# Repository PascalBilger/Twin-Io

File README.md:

# Twin-Io
A wireless multi lead ECG

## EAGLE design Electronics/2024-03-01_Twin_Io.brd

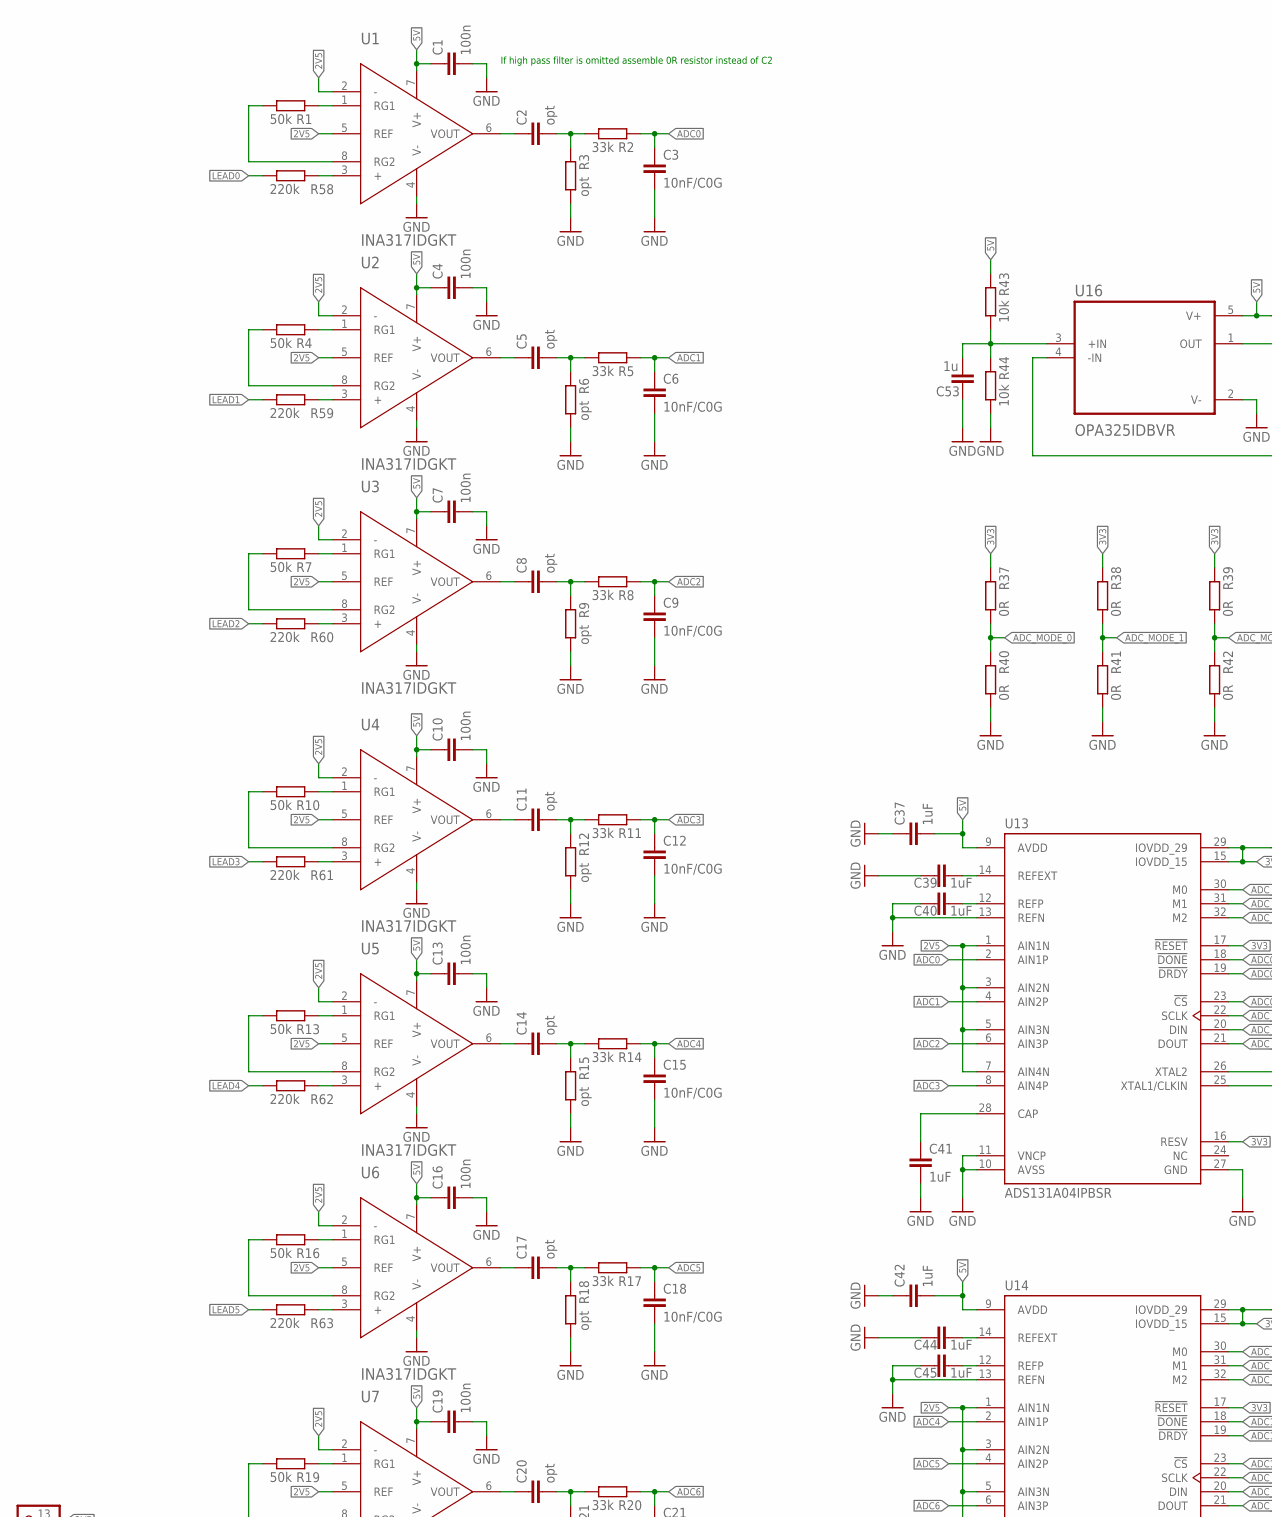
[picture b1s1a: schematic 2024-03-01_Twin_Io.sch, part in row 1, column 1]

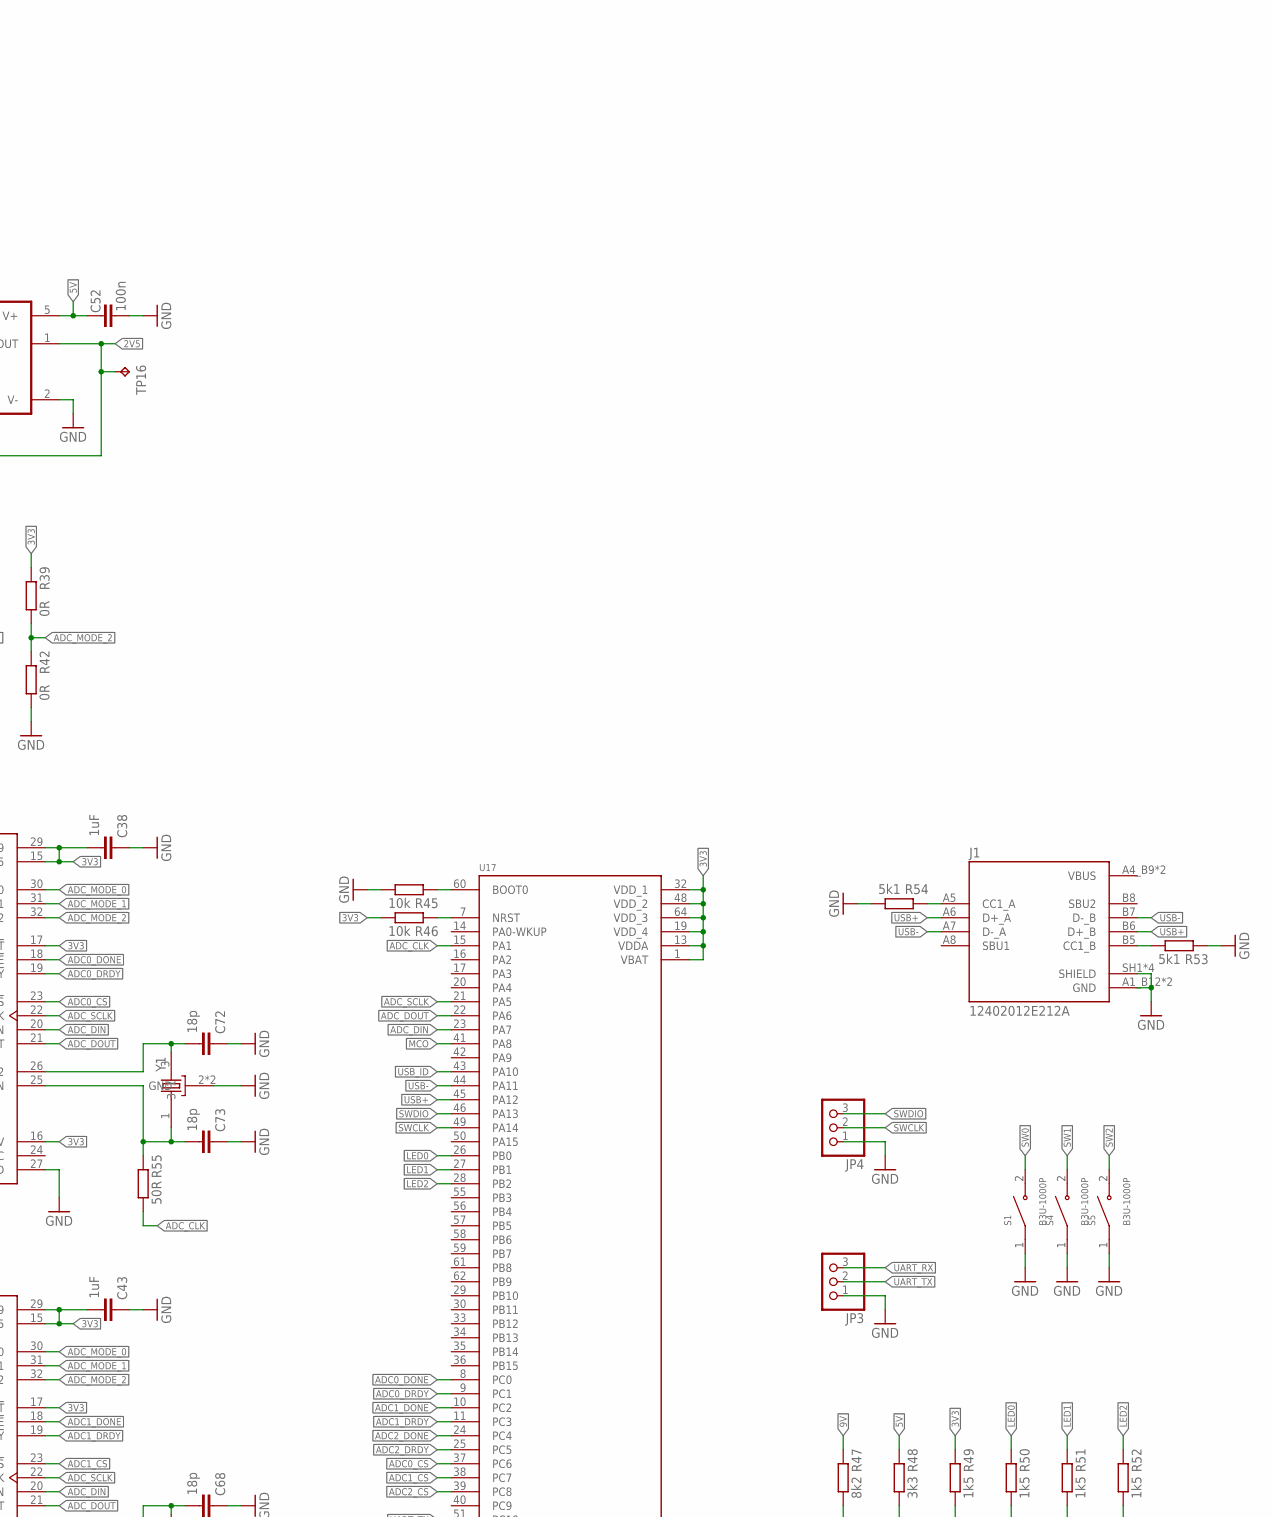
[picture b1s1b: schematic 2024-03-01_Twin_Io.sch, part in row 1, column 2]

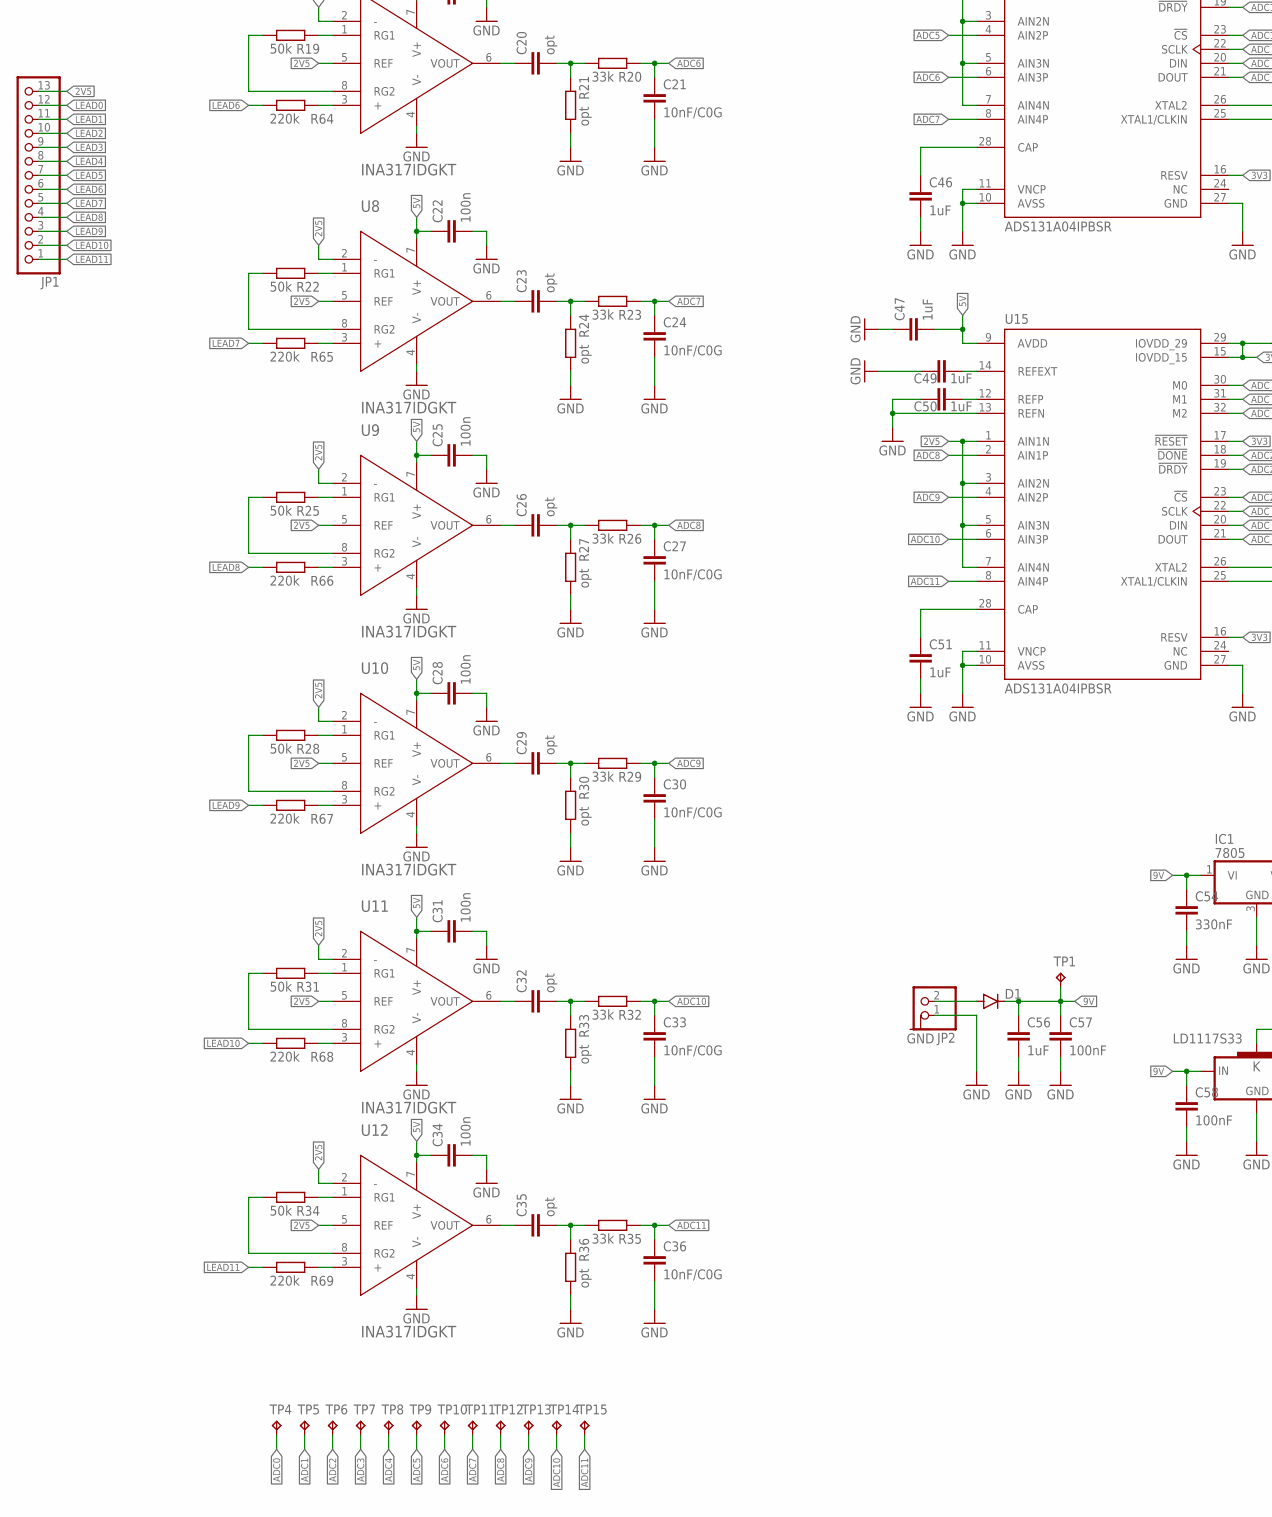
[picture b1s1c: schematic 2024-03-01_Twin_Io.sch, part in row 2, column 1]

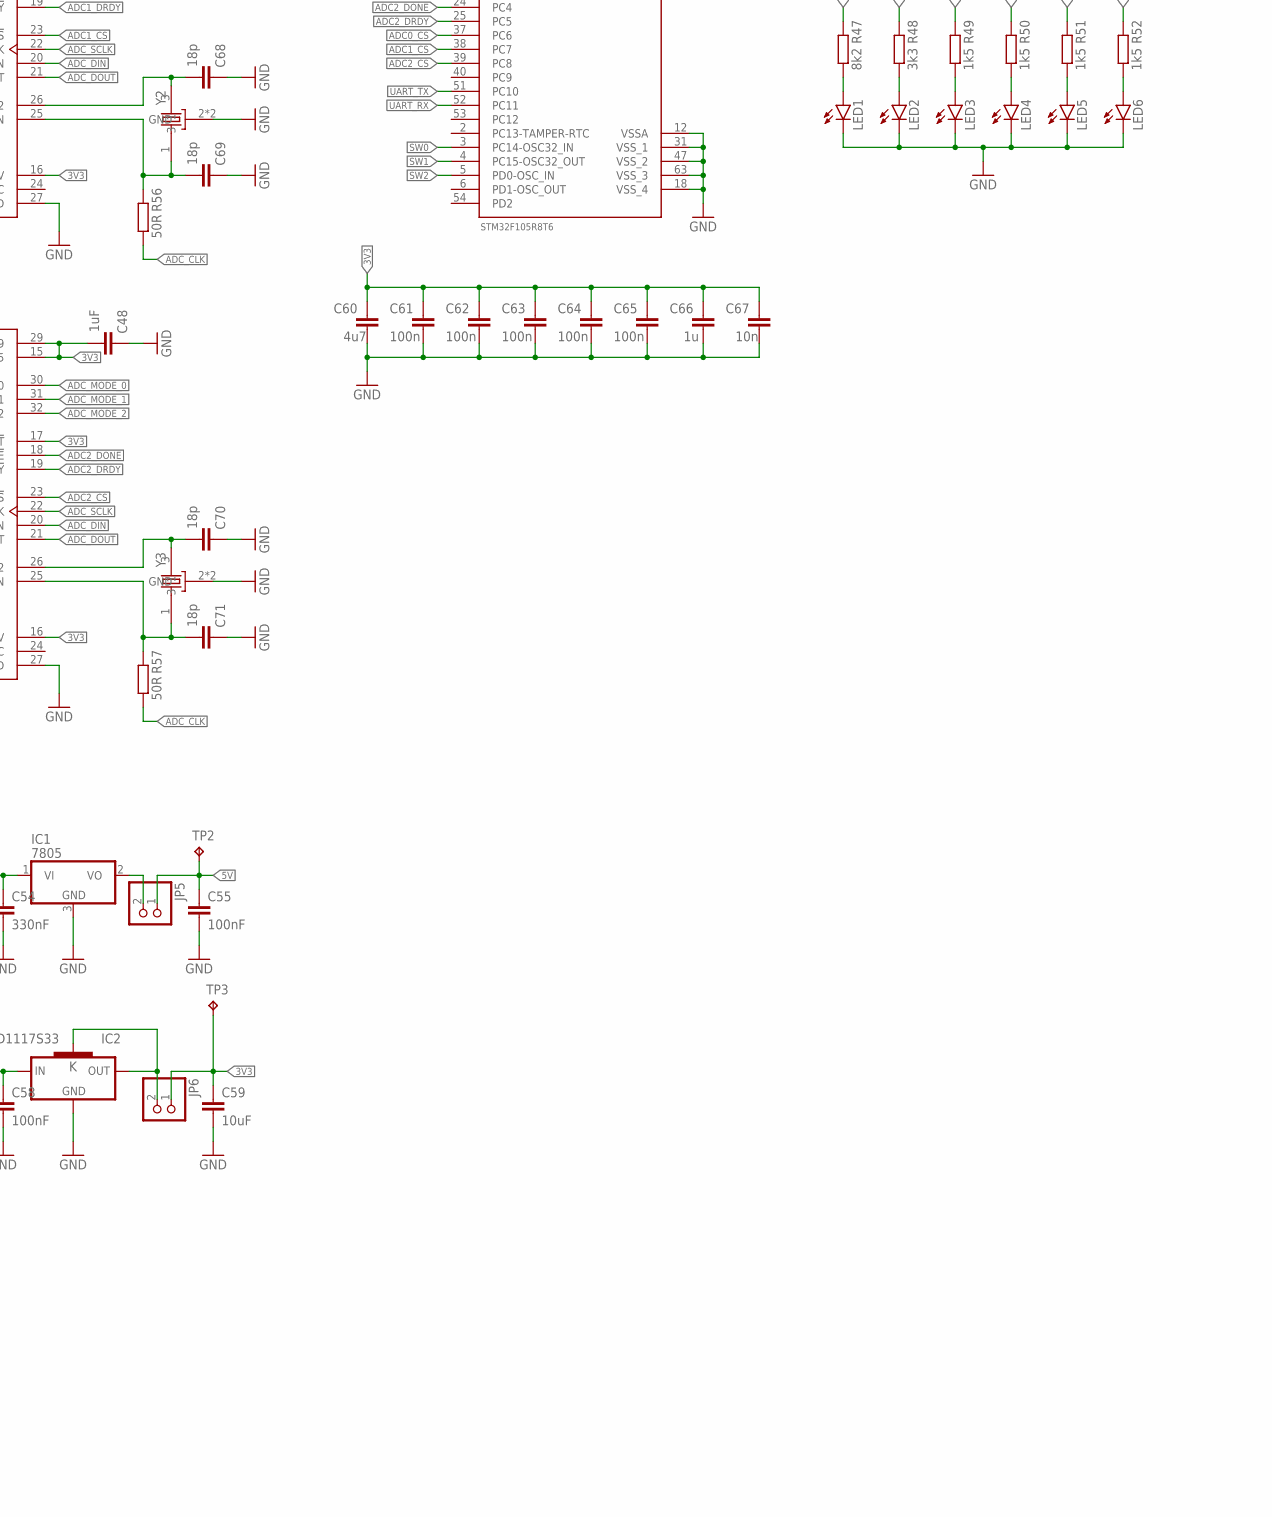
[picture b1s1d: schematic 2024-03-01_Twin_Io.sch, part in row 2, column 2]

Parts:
C1, C4, C7, C10, C13, C16, C19, C22, C25, C28, C31, C34, C52, C61, C62, C63, C64, C65: 100n; C0603
C2, C5, C8, C11, C14, C17, C20, C23, C26, C29, C32, C35: opt; C0603
C3, C6, C9, C12, C15, C18, C21, C24, C27, C30, C33, C36: 10nF/C0G; C0603
C37, C38, C39, C40, C41, C42, C43, C44, C45, C46, C47, C48, C49, C50, C51, C56: 1uF; C0603
C53, C66: 1u; C0603
C54: 330nF; C0603
C55, C57, C58: 100nF; C0603
C59: 10uF; C0603
C60: 4u7; C0603
C67: 10n; C0603
C68, C69, C70, C71, C72, C73: 18p; C0603
D1: DIODE-DO214AA; DO214AA
IC1: 7805; TO252
IC2: LD1117S33; SOT223
J1: 12402012E212A; AMPHENOL_12402012E212A
JP1: PINHD-1X13; 1X13
JP2, JP5, JP6: PINHD-1X2; 1X02
JP3, JP4: PINHD-1X3; 1X03
LED1, LED2, LED3, LED4, LED5, LED6: LEDSML1206; SML1206
R1, R4, R7, R10, R13, R16, R19, R22, R25, R28, R31, R34: 50k; R0603
R2, R5, R8, R11, R14, R17, R20, R23, R26, R29, R32, R35: 33k; R0603
R3, R6, R9, R12, R15, R18, R21, R24, R27, R30, R33, R36: opt; R0603
R37, R38, R39, R40, R41, R42: 0R; R0603
R43, R44, R45, R46: 10k; R0603
R47: 8k2; R0603
R48: 3k3; R0603
R49, R50, R51, R52: 1k5; R0603
R53, R54: 5k1; R0603
R55, R56, R57: 50R; R0603
R58, R59, R60, R61, R62, R63, R64, R65, R66, R67, R68, R69: 220k; R0603
S1, S4, S5: B3U-1000P; SW_B3U-1000P
TP1, TP2, TP3, TP4, TP5, TP6, TP7, TP8, TP9, TP10, TP11, TP12, TP13, TP14, TP15, TP16: TPPAD1-17; P1-17
U1, U2, U3, U4, U5, U6, U7, U8, U9, U10, U11, U12: INA317IDGKT; SOP65P490X110-8N
U13, U14, U15: ADS131A04IPBSR; QFP50P700X700X120-32N
U16: OPA325IDBVR; SOT95P280X145-5N
U17: STM32F105R8T6; QFP50P1200X1200X160-64N
Y1, Y2, Y3: ABM3C-16.384MHZ-D4Y-T; OSCCC500X320X110-4N

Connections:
2V5: JP1.13, TP16.TP, U1.2 (-), U1.5 (REF), U2.2 (-), U2.5 (REF), U3.2 (-), U3.5 (REF), U4.2 (-), U4.5 (REF), U5.2 (-), U5.5 (REF), U6.2 (-), U6.5 (REF), U7.2 (-), U7.5 (REF), U8.2 (-), U8.5 (REF), U9.2 (-), U9.5 (REF), U10.2 (-), U10.5 (REF), U11.2 (-), U11.5 (REF), U12.2 (-), U12.5 (REF), U13.1 (AIN1N), U13.3 (AIN2N), U13.5 (AIN3N), U13.7 (AIN4N), U14.1 (AIN1N), U14.3 (AIN2N), U14.5 (AIN3N), U14.7 (AIN4N), U15.1 (AIN1N), U15.3 (AIN2N), U15.5 (AIN3N), U15.7 (AIN4N), U16.1 (OUT), U16.4 (-IN)
3V3: C38.2, C43.2, C48.2, C59.1, C60.1, C61.1, C62.1, C63.1, C64.1, C65.1, C66.1, C67.1, JP6.1, R37.2, R38.2, R39.2, R46.1, R49.2, TP3.TP, U13.15 (IOVDD_15), U13.16 (RESV), U13.17 (!RESET), U13.29 (IOVDD_29), U14.15 (IOVDD_15), U14.16 (RESV), U14.17 (!RESET), U14.29 (IOVDD_29), U15.15 (IOVDD_15), U15.16 (RESV), U15.17 (!RESET), U15.29 (IOVDD_29), U17.1 (VBAT), U17.13 (VDDA), U17.19 (VDD_4), U17.32 (VDD_1), U17.48 (VDD_2), U17.64 (VDD_3)
5V: C1.1, C4.1, C7.1, C10.1, C13.1, C16.1, C19.1, C22.1, C25.1, C28.1, C31.1, C34.1, C37.2, C42.2, C47.2, C52.1, C55.1, JP5.1, R43.2, R48.2, TP2.TP, U1.7 (V+), U2.7 (V+), U3.7 (V+), U4.7 (V+), U5.7 (V+), U6.7 (V+), U7.7 (V+), U8.7 (V+), U9.7 (V+), U10.7 (V+), U11.7 (V+), U12.7 (V+), U13.9 (AVDD), U14.9 (AVDD), U15.9 (AVDD), U16.5 (V+)
9V: C54.1, C56.1, C57.1, C58.1, D1.C, IC1.1 (VI), IC2.3 (IN), R47.2, TP1.TP
ADC0: C3.1, R2.2, TP4.TP, U13.2 (AIN1P)
ADC0_CS: U13.23 (!CS), U17.37 (PC6)
ADC0_DONE: U13.18 (!DONE), U17.8 (PC0)
ADC0_DRDY: U13.19 (!DRDY), U17.9 (PC1)
ADC1: C6.1, R5.2, TP5.TP, U13.4 (AIN2P)
ADC1_CS: U14.23 (!CS), U17.38 (PC7)
ADC1_DONE: U14.18 (!DONE), U17.10 (PC2)
ADC1_DRDY: U14.19 (!DRDY), U17.11 (PC3)
ADC2: C9.1, R8.2, TP6.TP, U13.6 (AIN3P)
ADC2_CS: U15.23 (!CS), U17.39 (PC8)
ADC2_DONE: U15.18 (!DONE), U17.24 (PC4)
ADC2_DRDY: U15.19 (!DRDY), U17.25 (PC5)
ADC3: C12.1, R11.2, TP7.TP, U13.8 (AIN4P)
ADC4: C15.1, R14.2, TP8.TP, U14.2 (AIN1P)
ADC5: C18.1, R17.2, TP9.TP, U14.4 (AIN2P)
ADC6: C21.1, R20.2, TP10.TP, U14.6 (AIN3P)
ADC7: C24.1, R23.2, TP11.TP, U14.8 (AIN4P)
ADC8: C27.1, R26.2, TP12.TP, U15.2 (AIN1P)
ADC9: C30.1, R29.2, TP13.TP, U15.4 (AIN2P)
ADC10: C33.1, R32.2, TP14.TP, U15.6 (AIN3P)
ADC11: C36.1, R35.2, TP15.TP, U15.8 (AIN4P)
ADC_CLK: R55.1, R56.1, R57.1, U17.15 (PA1)
ADC_DIN: U13.20 (DIN), U14.20 (DIN), U15.20 (DIN), U17.23 (PA7)
ADC_DOUT: U13.21 (DOUT), U14.21 (DOUT), U15.21 (DOUT), U17.22 (PA6)
ADC_MODE_0: R37.1, R40.2, U13.30 (M0), U14.30 (M0), U15.30 (M0)
ADC_MODE_1: R38.1, R41.2, U13.31 (M1), U14.31 (M1), U15.31 (M1)
ADC_MODE_2: R39.1, R42.2, U13.32 (M2), U14.32 (M2), U15.32 (M2)
ADC_SCLK: U13.22 (SCLK), U14.22 (SCLK), U15.22 (SCLK), U17.21 (PA5)
GND: C1.2, C3.2, C4.2, C6.2, C7.2, C9.2, C10.2, C12.2, C13.2, C15.2, C16.2, C18.2, C19.2, C21.2, C22.2, C24.2, C25.2, C27.2, C28.2, C30.2, C31.2, C33.2, C34.2, C36.2, C37.1, C38.1, C39.1, C40.1, C41.2, C42.1, C43.1, C44.1, C45.1, C46.2, C47.1, C48.1, C49.1, C50.1, C51.2, C52.2, C53.1, C54.2, C55.2, C56.2, C57.2, C58.2, C59.2, C60.2, C61.2, C62.2, C63.2, C64.2, C65.2, C66.2, C67.2, C68.1, C69.1, C70.1, C71.1, C72.1, C73.1, IC1.3 (GND), IC2.1 (GND), J1.A1_B12 (GND), J1.B1_A12 (GND), J1.SH1 (SHIELD), J1.SH2 (SHIELD), J1.SH3 (SHIELD), J1.SH4 (SHIELD), JP2.1, JP3.1, JP4.1, LED1.C, LED2.C, LED3.C, LED4.C, LED5.C, LED6.C, R3.1, R6.1, R9.1, R12.1, R15.1, R18.1, R21.1, R24.1, R27.1, R30.1, R33.1, R36.1, R40.1, R41.1, R42.1, R44.1, R45.1, R53.2, R54.1, S1.1, S4.1, S5.1, U1.4 (V-), U2.4 (V-), U3.4 (V-), U4.4 (V-), U5.4 (V-), U6.4 (V-), U7.4 (V-), U8.4 (V-), U9.4 (V-), U10.4 (V-), U11.4 (V-), U12.4 (V-), U13.10 (AVSS), U13.11 (VNCP), U13.13 (REFN), U13.27 (GND), U14.10 (AVSS), U14.11 (VNCP), U14.13 (REFN), U14.27 (GND), U15.10 (AVSS), U15.11 (VNCP), U15.13 (REFN), U15.27 (GND), U16.2 (V-), U17.12 (VSSA), U17.18 (VSS_4), U17.31 (VSS_1), U17.47 (VSS_2), U17.63 (VSS_3), Y1.2 (GND), Y1.4 (GND), Y2.2 (GND), Y2.4 (GND), Y3.2 (GND), Y3.4 (GND)
LEAD0: JP1.12, R58.1
LEAD1: JP1.11, R59.1
LEAD2: JP1.10, R60.1
LEAD3: JP1.9, R61.1
LEAD4: JP1.8, R62.1
LEAD5: JP1.7, R63.1
LEAD6: JP1.6, R64.1
LEAD7: JP1.5, R65.1
LEAD8: JP1.4, R66.1
LEAD9: JP1.3, R67.1
LEAD10: JP1.2, R68.1
LEAD11: JP1.1, R69.1
LED0: R50.2, U17.26 (PB0)
LED1: R51.2, U17.27 (PB1)
LED2: R52.2, U17.28 (PB2)
MCO: U17.41 (PA8)
unnamed: R1.2, U1.1 (RG1)
unnamed: R1.1, U1.8 (RG2)
unnamed: C2.1, U1.6 (VOUT)
unnamed: C2.2, R2.1, R3.2
unnamed: D1.A, JP2.2
unnamed: C41.1, U13.28 (CAP)
unnamed: C72.2, U13.26 (XTAL2), Y1.3
unnamed: C73.2, R55.2, U13.25 (XTAL1/CLKIN), Y1.1
unnamed: C40.2, U13.12 (REFP)
unnamed: C39.2, U13.14 (REFEXT)
unnamed: R4.2, U2.1 (RG1)
unnamed: R4.1, U2.8 (RG2)
unnamed: C5.1, U2.6 (VOUT)
unnamed: C5.2, R5.1, R6.2
unnamed: R7.2, U3.1 (RG1)
unnamed: R7.1, U3.8 (RG2)
unnamed: C8.1, U3.6 (VOUT)
unnamed: C8.2, R8.1, R9.2
unnamed: R10.2, U4.1 (RG1)
unnamed: R10.1, U4.8 (RG2)
unnamed: C11.1, U4.6 (VOUT)
unnamed: C11.2, R11.1, R12.2
unnamed: R13.2, U5.1 (RG1)
unnamed: R13.1, U5.8 (RG2)
unnamed: C14.1, U5.6 (VOUT)
unnamed: C14.2, R14.1, R15.2
unnamed: R16.2, U6.1 (RG1)
unnamed: R16.1, U6.8 (RG2)
unnamed: C17.1, U6.6 (VOUT)
unnamed: C17.2, R17.1, R18.2
unnamed: R19.2, U7.1 (RG1)
unnamed: R19.1, U7.8 (RG2)
unnamed: C20.1, U7.6 (VOUT)
unnamed: C20.2, R20.1, R21.2
unnamed: R22.2, U8.1 (RG1)
unnamed: R22.1, U8.8 (RG2)
unnamed: C23.1, U8.6 (VOUT)
unnamed: C23.2, R23.1, R24.2
unnamed: R25.2, U9.1 (RG1)
unnamed: R25.1, U9.8 (RG2)
unnamed: C26.1, U9.6 (VOUT)
unnamed: C26.2, R26.1, R27.2
unnamed: C69.2, R56.2, U14.25 (XTAL1/CLKIN), Y2.1
unnamed: C46.1, U14.28 (CAP)
unnamed: C44.2, U14.14 (REFEXT)
unnamed: C68.2, U14.26 (XTAL2), Y2.3
unnamed: C45.2, U14.12 (REFP)
unnamed: C70.2, U15.26 (XTAL2), Y3.3
unnamed: C51.1, U15.28 (CAP)
unnamed: C49.2, U15.14 (REFEXT)
unnamed: C71.2, R57.2, U15.25 (XTAL1/CLKIN), Y3.1
unnamed: C50.2, U15.12 (REFP)
unnamed: R28.2, U10.1 (RG1)
unnamed: R28.1, U10.8 (RG2)
unnamed: C29.1, U10.6 (VOUT)
unnamed: C29.2, R29.1, R30.2
unnamed: R31.2, U11.1 (RG1)
unnamed: R31.1, U11.8 (RG2)
unnamed: C32.1, U11.6 (VOUT)
unnamed: C32.2, R32.1, R33.2
unnamed: R34.2, U12.1 (RG1)
unnamed: R34.1, U12.8 (RG2)
unnamed: C35.1, U12.6 (VOUT)
unnamed: C35.2, R35.1, R36.2
unnamed: R45.2, U17.60 (BOOT0)
unnamed: R46.2, U17.7 (NRST)
unnamed: C53.2, R43.1, R44.2, U16.3 (+IN)
unnamed: LED1.A, R47.1
unnamed: LED2.A, R48.1
unnamed: LED3.A, R49.1
unnamed: LED4.A, R50.1
unnamed: LED5.A, R51.1
unnamed: LED6.A, R52.1
unnamed: J1.A5 (CC1_A), R54.2
unnamed: J1.B5 (CC1_B), R53.1
unnamed: IC1.2 (VO), JP5.2
unnamed: R58.2, U1.3 (+)
unnamed: IC2.2 (OUT), IC2.4 (K), JP6.2
unnamed: R59.2, U2.3 (+)
unnamed: R60.2, U3.3 (+)
unnamed: R61.2, U4.3 (+)
unnamed: R62.2, U5.3 (+)
unnamed: R63.2, U6.3 (+)
unnamed: R64.2, U7.3 (+)
unnamed: R65.2, U8.3 (+)
unnamed: R66.2, U9.3 (+)
unnamed: R67.2, U10.3 (+)
unnamed: R68.2, U11.3 (+)
unnamed: R69.2, U12.3 (+)
SW0: S1.2, U17.3 (PC14-OSC32_IN)
SW1: S4.2, U17.4 (PC15-OSC32_OUT)
SW2: S5.2, U17.5 (PD0-OSC_IN)
SWCLK: JP4.2, U17.49 (PA14)
SWDIO: JP4.3, U17.46 (PA13)
UART_RX: JP3.3, U17.52 (PC11)
UART_TX: JP3.2, U17.51 (PC10)
USB+: J1.A6 (D+_A), J1.B6 (D+_B), U17.45 (PA12)
USB-: J1.A7 (D-_A), J1.B7 (D-_B), U17.44 (PA11)
USB_ID: U17.43 (PA10)
VBUS: J1.A4_B9 (VBUS), J1.B4_A9 (VBUS)

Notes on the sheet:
If high pass filter is omitted assemble 0R resistor instead of C2

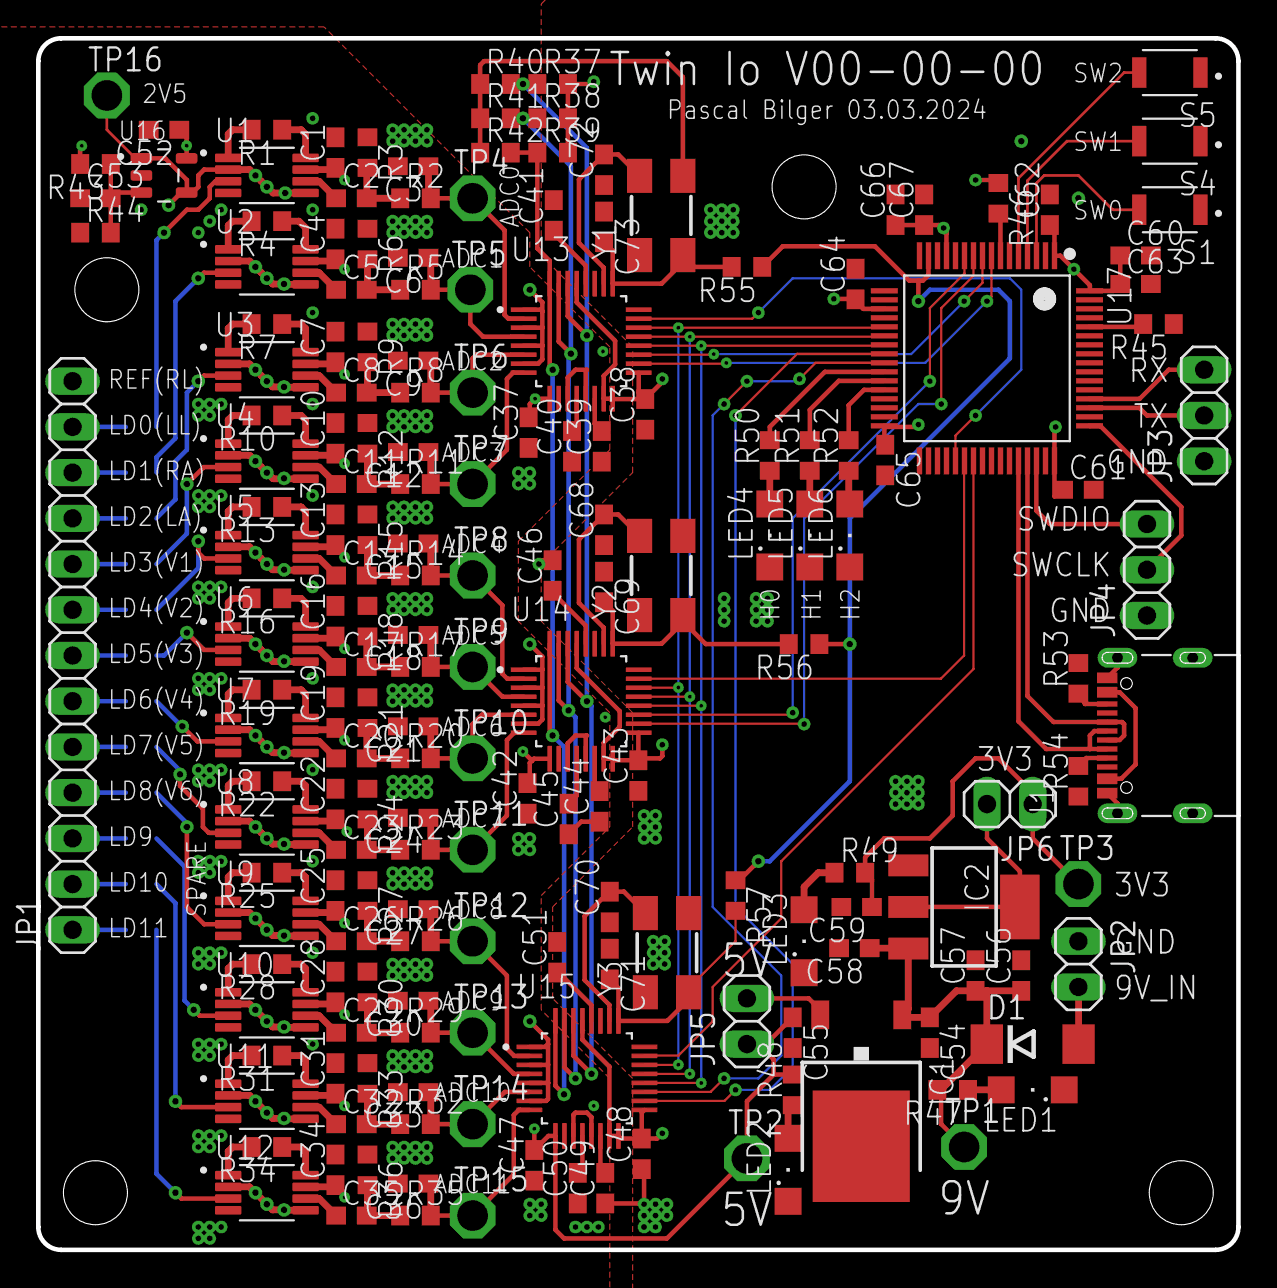
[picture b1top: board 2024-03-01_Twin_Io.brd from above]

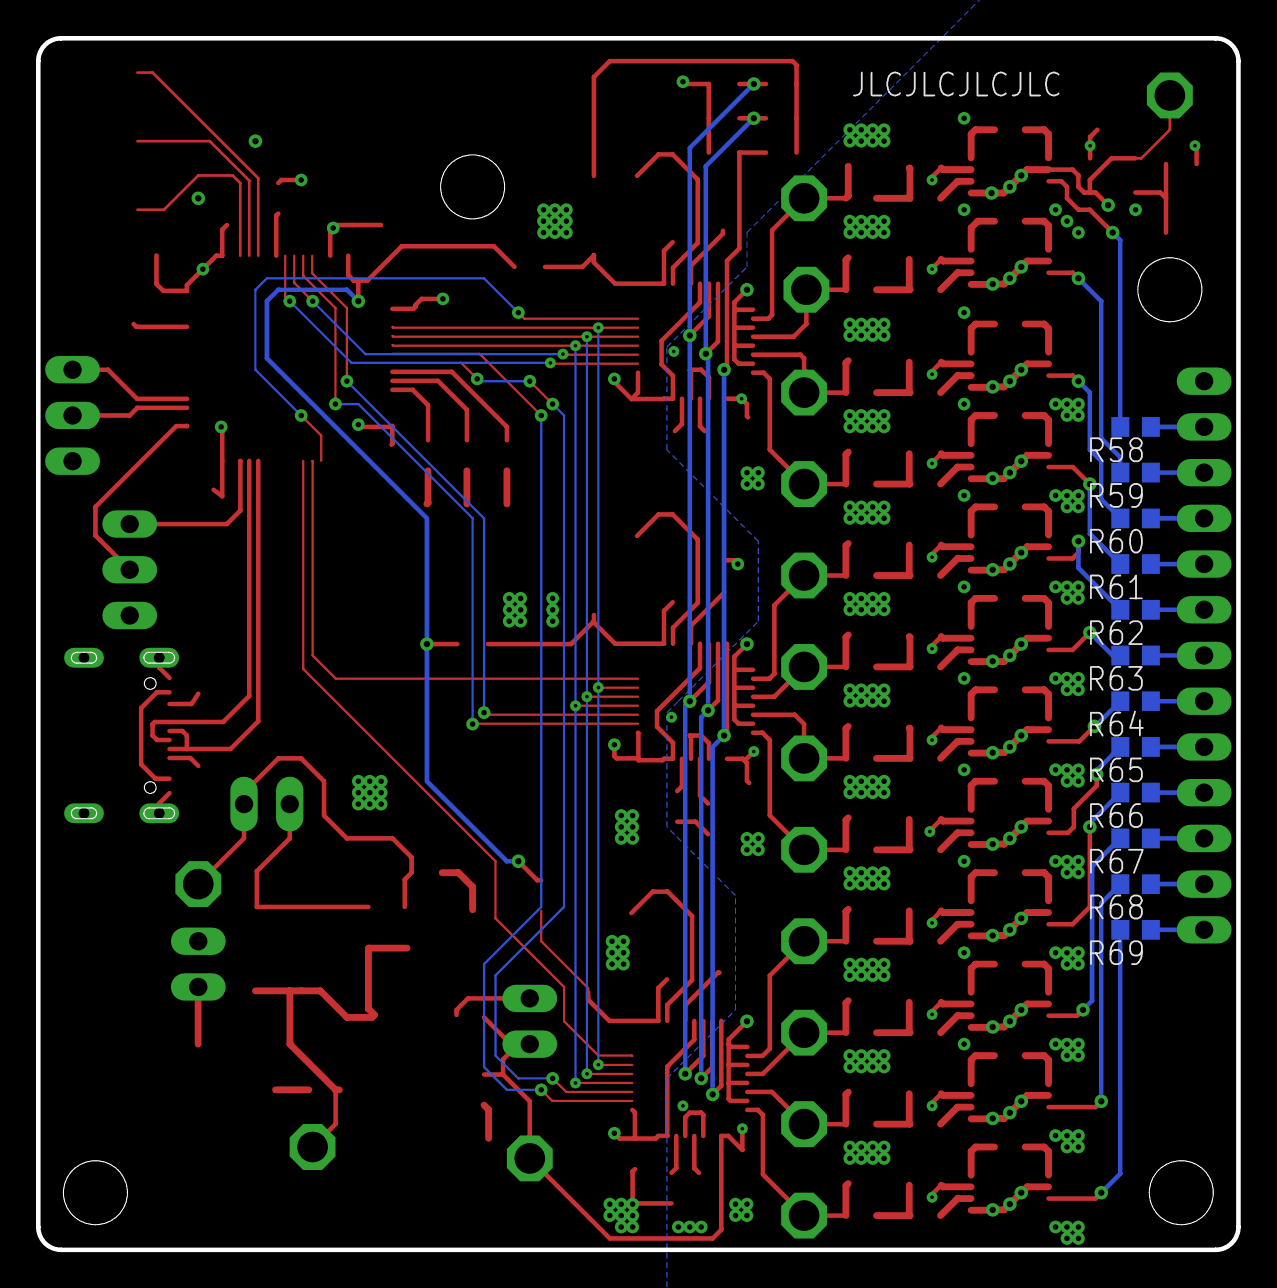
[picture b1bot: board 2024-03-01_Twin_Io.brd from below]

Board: 4 copper layers, 66.7 x 67.3 mm, 197 parts (12 on the bottom side), 147 nets.

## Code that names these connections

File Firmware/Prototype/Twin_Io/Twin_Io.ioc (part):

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Mcu.Name=STM32F105R(8-B-C)Tx
Mcu.Package=LQFP64
Mcu.UserName=STM32F105R8Tx
PA1.Signal=S_TIM2_CH2
PA10.Mode=Asynchronous
PA10.Signal=USART1_RX
PA13.Mode=Serial_Wire
PA13.Signal=SYS_JTMS-SWDIO
PA14.Mode=Serial_Wire
PA14.Signal=SYS_JTCK-SWCLK
PA5.Mode=Full_Duplex_Master
PA5.Signal=SPI1_SCK
PA6.Mode=Full_Duplex_Master
PA6.Signal=SPI1_MISO
PA7.Mode=Full_Duplex_Master
PA7.Signal=SPI1_MOSI
PA9.Mode=Asynchronous
PA9.Signal=USART1_TX
PB0.GPIOParameters=GPIO_Label
PB0.GPIO_Label=LED0
PB0.Signal=GPIO_Output
PB1.GPIOParameters=GPIO_Label
PB1.GPIO_Label=LED1
PB1.Signal=GPIO_Output
PB2.GPIOParameters=GPIO_Label
PB2.GPIO_Label=LED2
PB2.Signal=GPIO_Output
PC0.GPIOParameters=GPIO_PuPd,GPIO_Label
PC0.GPIO_Label=ADC0_DONE
PC0.GPIO_PuPd=GPIO_PULLUP
PC0.Signal=GPIO_Input
PC1.GPIOParameters=GPIO_PuPd,GPIO_Label,GPIO_ModeDefaultEXTI
PC1.GPIO_Label=ADC0_DRDY
PC1.GPIO_ModeDefaultEXTI=GPIO_MODE_IT_FALLING
PC1.GPIO_PuPd=GPIO_PULLUP
PC1.Signal=GPXTI1
PC10.Mode=Asynchronous
PC10.Signal=USART3_TX
PC11.Mode=Asynchronous
PC11.Signal=USART3_RX
PC14-OSC32_IN.GPIOParameters=GPIO_Label
PC14-OSC32_IN.GPIO_Label=SW0
PC14-OSC32_IN.Signal=GPIO_Input
PC15-OSC32_OUT.GPIOParameters=GPIO_Label
PC15-OSC32_OUT.GPIO_Label=SW1
PC15-OSC32_OUT.Signal=GPIO_Input
PC2.GPIOParameters=GPIO_PuPd,GPIO_Label
PC2.GPIO_Label=ADC1_DONE
PC2.GPIO_PuPd=GPIO_PULLUP
PC2.Signal=GPIO_Input
PC3.GPIOParameters=GPIO_PuPd,GPIO_Label,GPIO_ModeDefaultEXTI
PC3.GPIO_Label=ADC1_DRDY
PC3.GPIO_ModeDefaultEXTI=GPIO_MODE_IT_FALLING
PC3.GPIO_PuPd=GPIO_PULLUP
PC3.Signal=GPXTI3
PC4.GPIOParameters=GPIO_PuPd,GPIO_Label
PC4.GPIO_Label=ADC2_DONE
PC4.GPIO_PuPd=GPIO_PULLUP
PC4.Signal=GPIO_Input
PC5.GPIOParameters=GPIO_PuPd,GPIO_Label,GPIO_ModeDefaultEXTI
PC5.GPIO_Label=ADC2_DRDY
PC5.GPIO_ModeDefaultEXTI=GPIO_MODE_IT_FALLING
PC5.GPIO_PuPd=GPIO_PULLUP
PC5.Signal=GPXTI5
PC6.GPIOParameters=GPIO_Label
PC6.GPIO_Label=ADC0_CS
PC6.Signal=GPIO_Output
PC7.GPIOParameters=GPIO_Label
PC7.GPIO_Label=ADC1_CS
PC7.Signal=GPIO_Output
PC8.GPIOParameters=GPIO_Label
PC8.GPIO_Label=ADC2_CS
PC8.Signal=GPIO_Output
PD0-OSC_IN.Mode=HSE-External-Oscillator
PD0-OSC_IN.Signal=RCC_OSC_IN
PD1-OSC_OUT.Mode=HSE-External-Oscillator
PD1-OSC_OUT.Signal=RCC_OSC_OUT
RCC.HSEDivPLL=RCC_HSE_PREDIV_DIV2
RCC.HSE_VALUE=16384000
RCC.SYSCLKFreq_VALUE=65536000
RCC.SYSCLKSource=RCC_SYSCLKSOURCE_PLLCLK
board=custom

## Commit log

2024-03-02 Added first version of schematic
2024-03-02 renamed all components and created board
2024-03-03 First Prototype Version of Schematic and PCB done
2024-03-03 Added Eagle Library for USB-C
2024-03-04 Renamed Schematic and Board with correct Year
2024-03-04 Created an adapter from AD8422 to INA317
2024-03-05 Added possibility for STM32 Timer output to be used for the ADC clock, selectable by 3x 0Ohm resistors
2024-03-06 Final changes for V00-00-00
2024-03-16 First working program (Tested with ADC0)
2024-03-16 Wrote a python program which extracts Channel 0 from ADC readings
2024-03-18 RawToCsv working for 12 Channels including filtering
2024-03-18 LiveView working with filtering for all 12 ADC channels
2024-03-18 Added a serial logger written in python which is able to read all the data at 3MBaud.
2024-03-18 Changed the compiler optimization from none to fast Code is now able to read the ADC at 2kHz and send it via 3MBaud to Serial. Attention: There is a bug which was not further investigated which mirro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
2024-03-18 Updated peripheral files
2024-03-18 Remove unused files
2024-03-18 Added gitignore to git
2024-03-18 Changed the Resistors which connect the STM32 to the clock input of the ADC from 0R to 50R
2024-03-18 Added pdf files of schematic and layout of the first prototype
2024-03-19 Added file with links and ressources
2024-03-19 Added all of the files which are auto generated by STM32CubeIDE to .gitignore
2024-03-19 Added files for STM32CubeIDE which are needed to compile the program. They were removed earlier because I thought they werent needed
2024-03-22 Lowered the SPI Baudrate from 16.384 to 4.096MBits/s which solved the problem with mirrored channels and general weird behavior. Caution: A Baudrate of 8.192MBits/s was also tested but resulted in th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
2024-03-22 Added output of all available COM ports and selection possibility to the Serial Logger script
2024-03-23 Restructured and commented python data analysis code
2024-03-23 - Added the option to LiveView to scale all graphs at the same time to analyze the data - Added calculation of the lead voltages from the electrodes - Added dc-offset removal - Added conversion from 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
2024-03-23 Fixed a bug. The configuration of the ADS131 which should have gone into register 0xC was written into register 0xB which resulted in the ADCs going into "power save" instead of "high resolution" mod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
2024-03-23 - Added a counter to display the current progress with analyzing the data - Fixed a bug which caused the time on the graph to always be from 0-10 seconds - Inverted how "AutoScaleYAxis" affects the b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
2024-11-14 Removed the pdfs because they will be in the release
